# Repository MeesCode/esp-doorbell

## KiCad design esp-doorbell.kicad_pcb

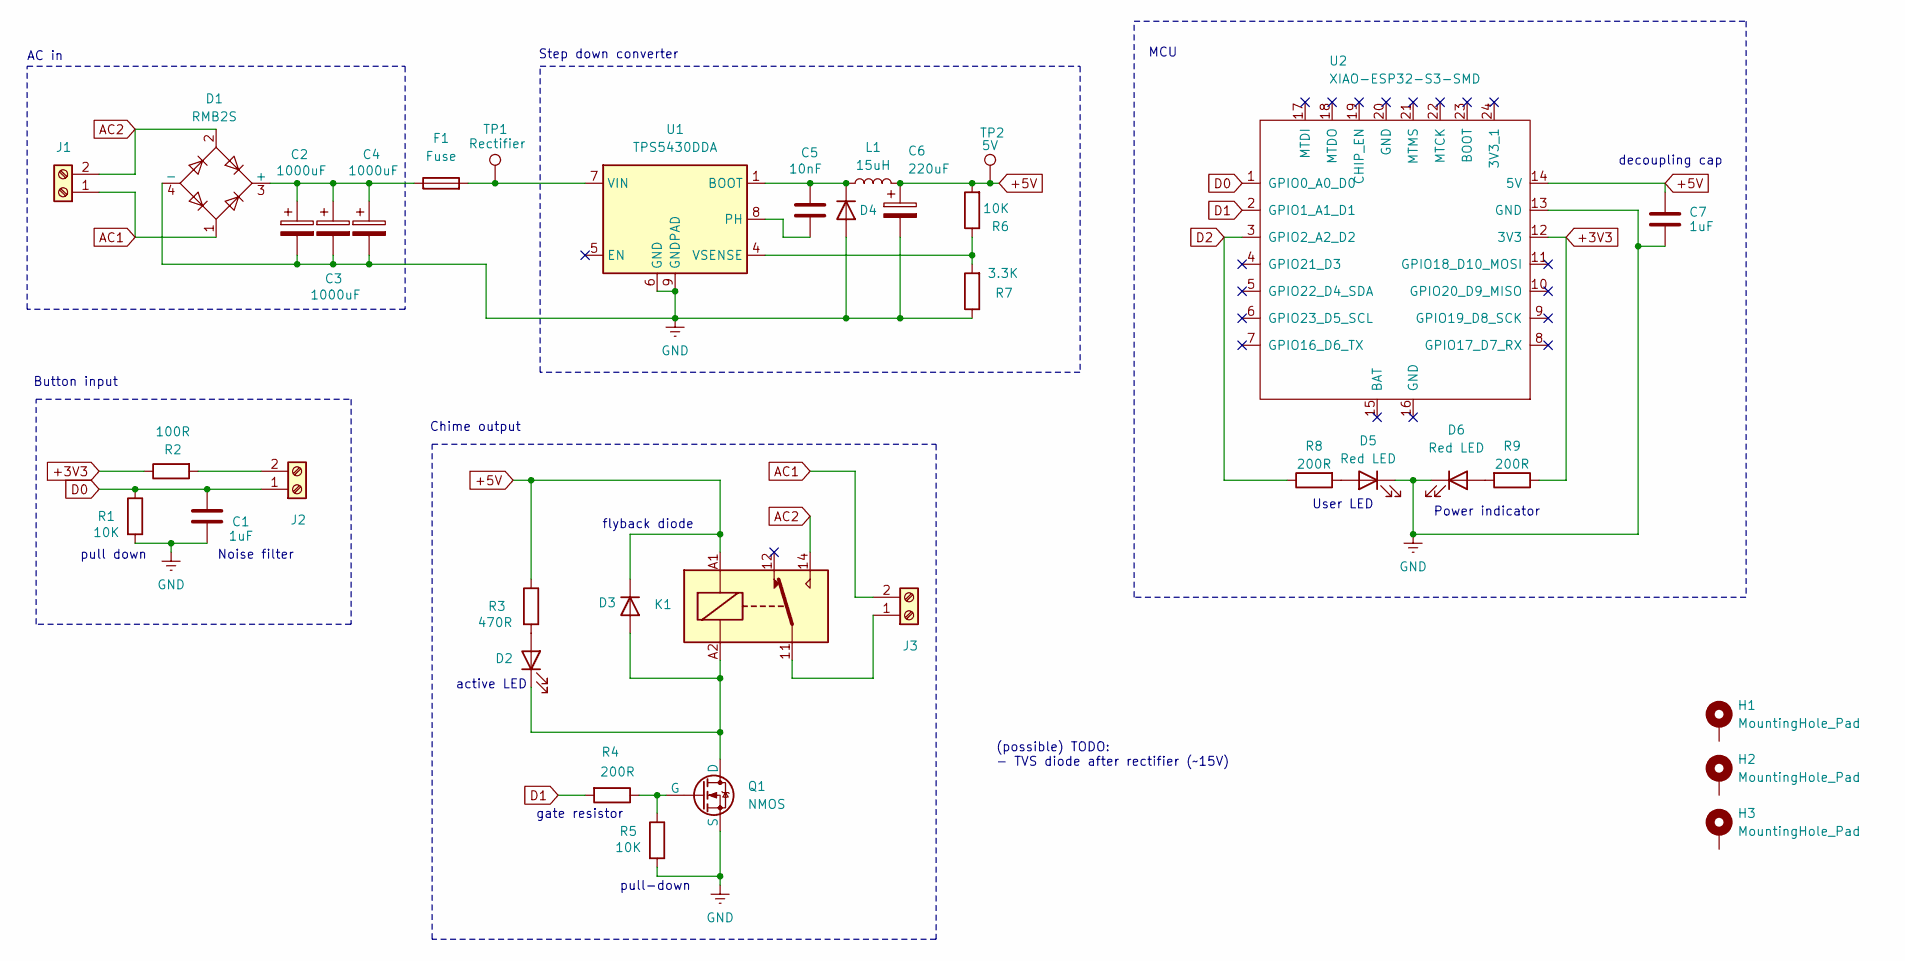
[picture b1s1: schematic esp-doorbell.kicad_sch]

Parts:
C1, C7: 1uF; C_0402_1005Metric; LCSC C52923
C2, C3, C4: 1000uF; CP_Elec_10x12.5; LCSC C2904877
C5: 10nF; C_0402_1005Metric; LCSC C57112
C6: 220uF; CP_Elec_6.3x7.7; LCSC C3342
D1: RMB2S; TO-269AA; LCSC C2488
D2, D5, D6: Red LED; LED_0603_1608Metric; LCSC C2286
D3: SM4007PL; D_SOD-123F; LCSC C64898
D4: D; D_SMA; Manufacturer # B530C-13-F; LCSC C64982
F1: Fuse; LED_1206_3216Metric; LCSC C720075
H1, H2, H3: MountingHole_Pad; MountingHole_3.2mm_M3_DIN965_Pad
J1, J2, J3: Screw_Terminal_01x02; TerminalBlock_Phoenix_MKDS-1,5-2-5.08_1x02_P5.08mm_Horizont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; LCSC C8465
K1: JQC-3FF-005-1Z; Relay_SPDT_Hongfa_JQC-3FF_0XX-1Z; LCSC C24585
L1: 15uH; L_Changjiang_FNR5040S; LCSC C167969
Q1: NMOS; SOT-23-3; LCSC C20917
R1, R5, R6: 10K; R_0603_1608Metric; LCSC C15401
R2: 100R; R_0603_1608Metric; LCSC C22775
R3: 470R; R_0603_1608Metric; LCSC C23179
R4, R8, R9: 200R; R_0603_1608Metric; LCSC C22962
R7: 3.3K; R_0603_1608Metric; LCSC C22978
TP1: Rectifier; TestPoint_Pad_D1.0mm
TP2: 5V; TestPoint_Pad_D1.0mm
U1: TPS5430DDA; TI_SO-PowerPAD-8_ThermalVias; LCSC C9864
U2: XIAO-ESP32-S3-SMD; XIAO-ESP32C6-SMD

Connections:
+3V3: R2.1, R9.1, U2.12 (3V3)
+5V: C6.1, C7.1, D3.1 (K), K1.A1, L1.2, R3.1, R6.2, TP2.1, U2.14 (5V)
AC1: D1.1, J1.1, J3.2
AC2: D1.2, J1.2, K1.14
D0: C1.1, J2.1, R1.1, U2.1 (GPIO0_A0_D0)
D1: R4.2, U2.2 (GPIO1_A1_D1)
D2: R8.1, U2.3 (GPIO2_A2_D2)
GND: C1.2, C2.2, C3.2, C4.2, C6.2, C7.2, D1.4 (-), D4.2 (A), D5.1 (K), D6.1 (K), Q1.3 (S), R1.2, R5.2, R7.1, U1.6 (GND), U1.9 (GNDPAD), U2.13 (GND)
unnamed: C2.1, C3.1, C4.1, D1.3 (+), F1.1
unnamed: D2.2 (A), R3.2
unnamed: D2.1 (K), D3.2 (A), K1.A2, Q1.1 (D)
unnamed: C5.2, D4.1 (K), L1.1, U1.1 (BOOT)
unnamed: D5.2 (A), R8.2
unnamed: D6.2 (A), R9.2
unnamed: J2.2, R2.2
unnamed: J3.1, K1.11
unnamed: Q1.2 (G), R4.1, R5.1
unnamed: C5.1, U1.8 (PH)
unnamed: F1.2, TP1.1, U1.7 (VIN)
unnamed: R6.1, R7.2, U1.4 (VSENSE)

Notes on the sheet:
active LED
Button input
Noise filter
Chime output
pull down
User LED
AC in
(possible) TODO: - TVS diode after rectifier (~15V)
Power indicator
gate resistor
pull-down
Step down converter
flyback diode
decoupling cap
MCU

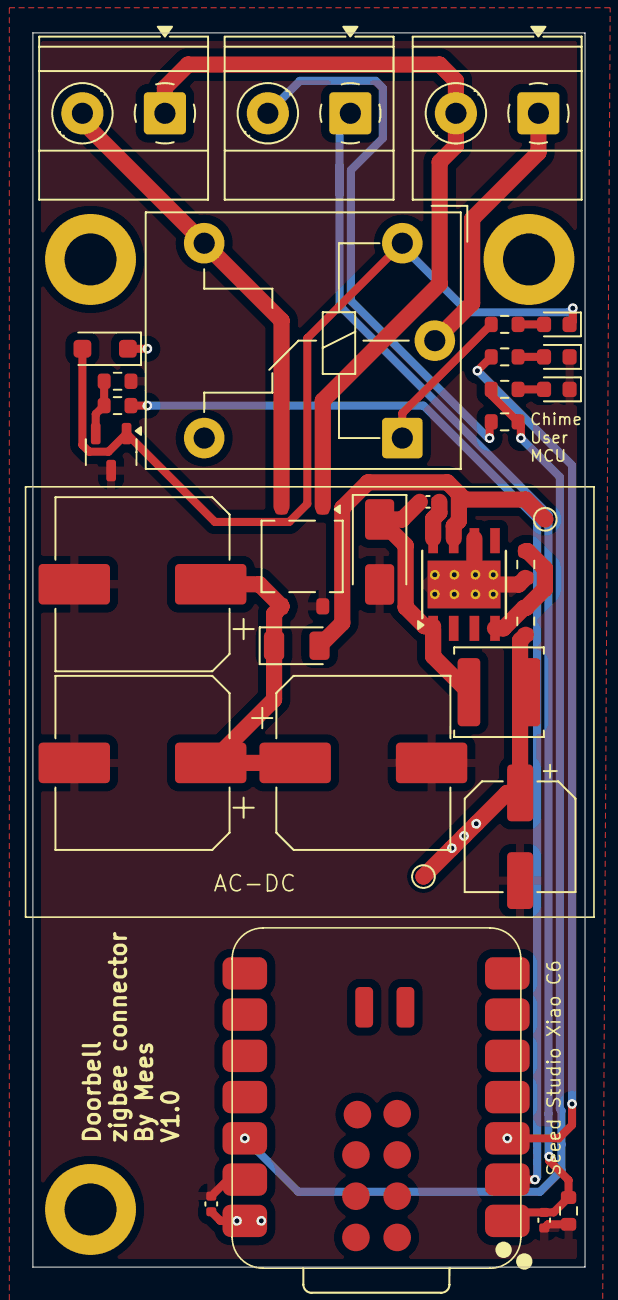
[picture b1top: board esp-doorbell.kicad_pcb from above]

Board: 2 copper layers, 34.0 x 76.0 mm, 36 parts (0 on the bottom side), 20 nets.

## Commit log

2025-04-15 initial schematics
2025-04-24 fix schematics, add layout
2025-04-25 make board a bit smaller
2025-04-25 save changes
2025-04-26 cleanup, add silkscreen
